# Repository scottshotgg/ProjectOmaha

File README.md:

# ProjectOmaha - Senior Design
## Software
### How to login
Authentication was recently added. Use username "admin" and password "password" to login.
### How to run the server
#### Windows
1. run `scripts/windows/run.bat`
2. If running for the first time, restart the command line and run again. (environment variables need to be refreshed)

#### Linux / OS X
Just execute `scripts/run`
### Debug Mode
Run the server in debug mode by executing `scripts/run -d 1`. If you're on windows, the command is `go run main.go -d 1`. Running in debug mode will cut out the microcontroller. All changes in state are just made in memory.

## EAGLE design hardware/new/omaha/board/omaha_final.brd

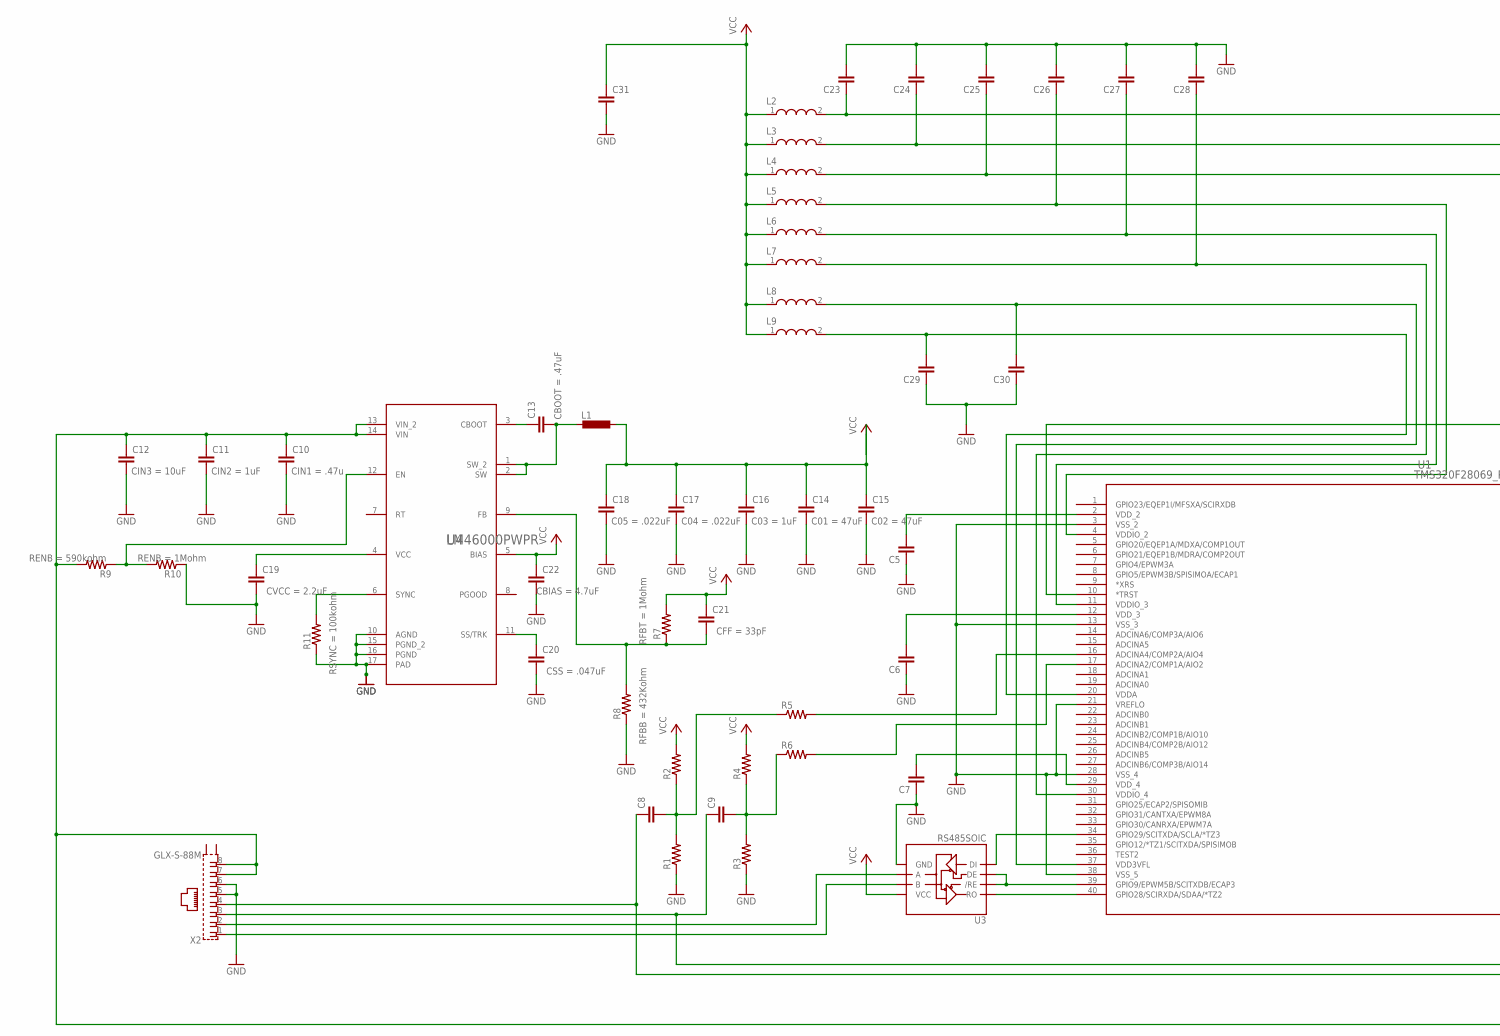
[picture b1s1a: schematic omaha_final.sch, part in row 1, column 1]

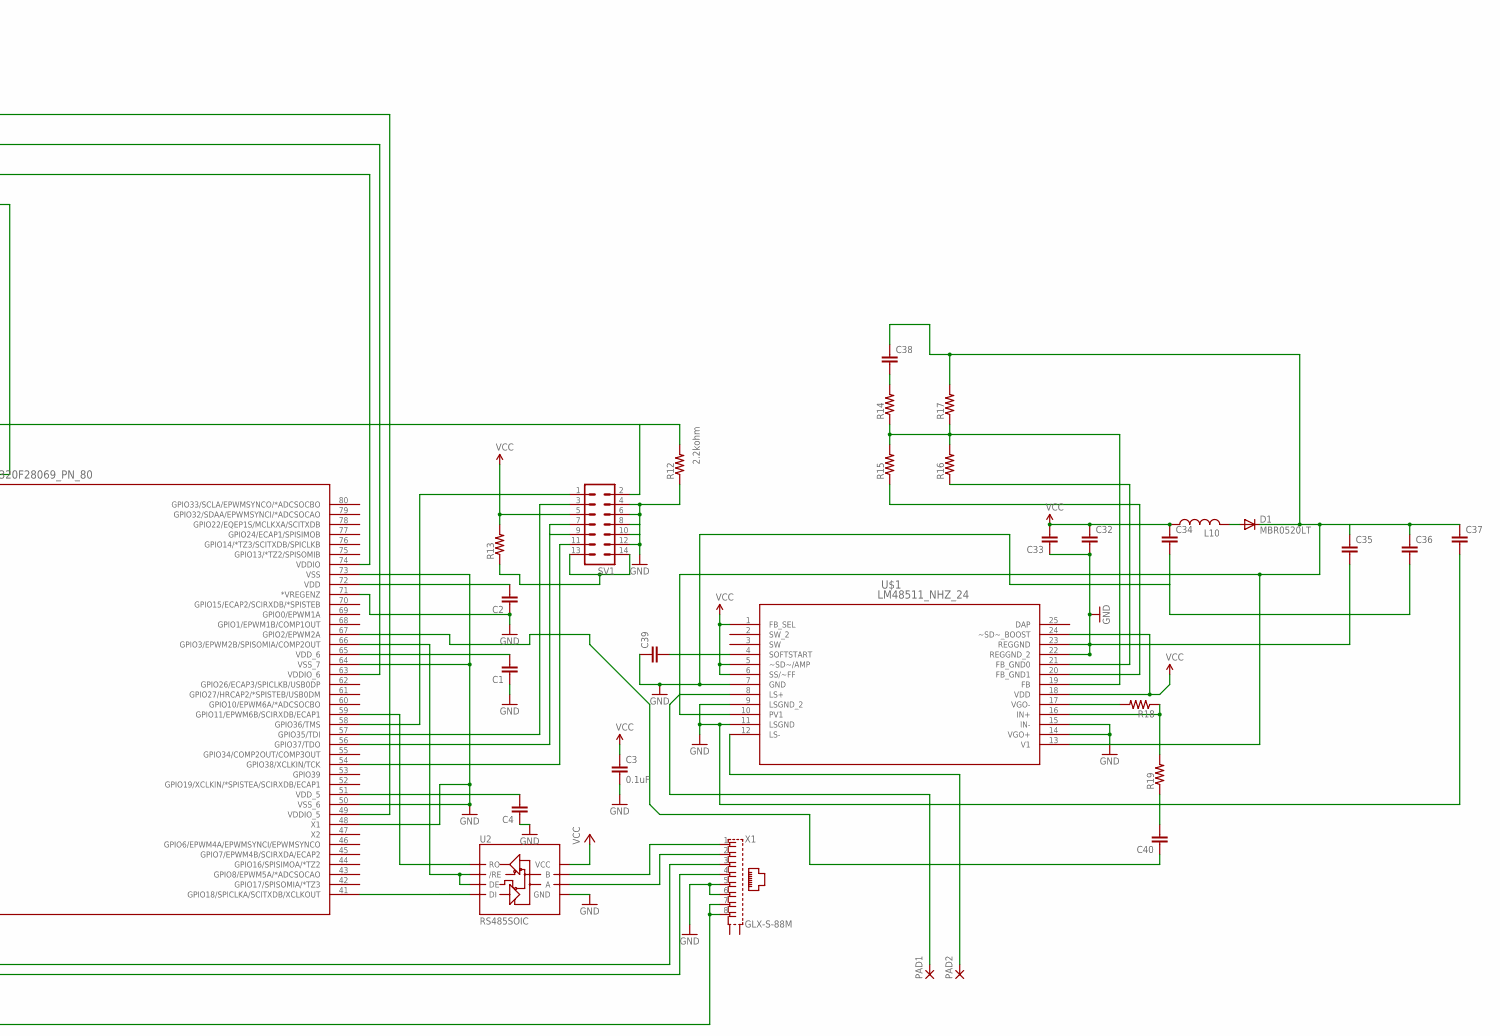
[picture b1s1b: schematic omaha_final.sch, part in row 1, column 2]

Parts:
C1, C2, C4, C5, C6, C7, C8, C9, C19, C20, C21, C23, C24, C25, C26, C27, C28, C29, C30, C31: C-EUC0603; C0603
C3: 0.1uF; 0603-CAP
C10, C13, C16, C17, C18, C22, C32, C33, C34, C35, C36, C37, C38, C39, C40: C-EUC0805; C0805
C11, C14, C15: C-EUC1210; C1210
C12: C-EUC2220K; C2220K
D1: MBR0520LT; SOD123
L1: DO3316P
L2, L3, L4, L5, L6, L7, L8, L9: WE-KI_0805A
L10: L-USL5650M; L5650M
PAD1, PAD2: 3,81/1,4
R1, R2, R3, R4, R5, R6, R7, R8, R9, R10, R11, R12, R13: R-US_R0603; R0603
R14, R15, R16, R17, R18, R19: R-US_R0805; R0805
SV1: MA07-2W
U1: TMS320F28069_PN_80; PN80
U2, U3: RS485SOIC; SO08
U4: LM46000PWPR; PWP0016F
U$1: LM48511_NHZ_24; SQA24B
X1, X2: GLX-S-88M

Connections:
DAP: U$1.25 (DAP)
GND: C1.1, C2.1, C3.2, C4.1, C5.1, C6.1, C7.1, C10.2, C11.2, C12.2, C14.2, C15.2, C16.2, C17.2, C18.2, C19.2, C20.2, C22.2, C23.2, C24.2, C25.2, C26.2, C27.2, C28.2, C29.1, C30.1, C31.2, C32.2, C33.1, C34.2, C35.2, C36.2, C37.2, C39.1, R1.1, R3.1, R8.1, R10.1, R11.1, R12.1, SV1.4, SV1.6, SV1.8, SV1.10, SV1.12, U1.3 (VSS_2), U1.13 (VSS_3), U1.21 (VREFLO), U1.28 (VSS_4), U1.38 (VSS_5), U1.48 (X1), U1.50 (VSS_6), U1.64 (VSS_7), U1.71 (*VREGENZ), U1.73 (VSS), U2.5 (GND), U3.5 (GND), U4.10 (AGND), U4.15 (PGND_2), U4.16 (PGND), U4.17 (PAD), U$1.7 (GND), U$1.9 (LSGND_2), U$1.11 (LSGND), U$1.14 (VGO+), U$1.15 (IN-), U$1.22 (REGGND_2), U$1.23 (REGGND), X1.5, X1.6, X2.5, X2.6
unnamed: U1.59 (GPIO11/EPWM6B/SCIRXDB/ECAP1), U2.1 (RO)
unnamed: U1.34 (GPIO29/SCITXDA/SCLA/*TZ3), U3.4 (DI)
unnamed: U1.41 (GPIO18/SPICLKA/SCITXDB/XCLKOUT), U2.4 (DI)
unnamed: U1.40 (GPIO28/SCIRXDA/SDAA/*TZ2), U3.1 (RO)
unnamed: C1.2, U1.65 (VDD_6)
unnamed: C2.2, U1.72 (VDD)
unnamed: C4.2, U1.51 (VDD_5)
unnamed: C5.2, U1.2 (VDD_2)
unnamed: C6.2, U1.12 (VDD_3)
unnamed: C7.2, U1.29 (VDD_4)
unnamed: U2.7 (B), X1.1
unnamed: U2.6 (A), X1.2
unnamed: U3.7 (B), X2.1
unnamed: U3.6 (A), X2.2
unnamed: C9.1, X1.3, X2.3
unnamed: C8.1, X1.4, X2.4
unnamed: C8.2, R1.2, R2.1, R5.1
unnamed: C9.2, R3.2, R4.1, R6.1
unnamed: R6.2, U1.17 (ADCINA2/COMP1A/AIO2)
unnamed: R5.2, U1.16 (ADCINA4/COMP2A/AIO4)
unnamed: C13.2, L1.1, U4.1 (SW_2), U4.2 (SW)
unnamed: C10.1, C11.1, C12.1, R9.2, U4.13 (VIN_2), U4.14 (VIN), X1.7, X1.8, X2.7, X2.8
unnamed: C13.1, U4.3 (CBOOT)
unnamed: C19.1, U4.4 (VCC)
unnamed: C20.1, U4.11 (SS/TRK)
unnamed: C21.2, R7.1, R8.2, U4.9 (FB)
unnamed: R9.1, R10.2, U4.12 (EN)
unnamed: R11.2, U4.6 (SYNC)
unnamed: SV1.3, U1.57 (GPIO35/TDI)
unnamed: C24.1, L3.2, U1.63 (VDDIO_6)
unnamed: C28.1, L7.2, U1.30 (VDDIO_4)
unnamed: C25.1, L4.2, U1.74 (VDDIO)
unnamed: SV1.7, SV1.9, U1.56 (GPIO37/TDO)
unnamed: SV1.11, U1.54 (GPIO38/XCLKIN/TCK)
unnamed: C30.2, L8.2, U1.37 (VDD3VFL)
unnamed: R13.1, SV1.13, SV1.14
unnamed: C27.1, L6.2, U1.11 (VDDIO_3)
unnamed: C26.1, L5.2, U1.4 (VDDIO_2)
unnamed: C29.2, L9.2, U1.20 (VDDA)
unnamed: C23.1, L2.2, U1.49 (VDDIO_5)
unnamed: R12.2, SV1.2, U1.10 (*TRST)
unnamed: SV1.1, U1.58 (GPIO36/TMS)
unnamed: U1.39 (GPIO9/EPWM5B/SCITXDB/ECAP3), U3.2 (/RE), U3.3 (DE)
unnamed: D1.A, L10.2
unnamed: C35.1, C36.1, C37.1, C38.1, D1.C, R17.2, U$1.10 (PV1), U$1.13 (V1)
unnamed: C40.2, R19.1
unnamed: C38.2, R14.2
unnamed: R14.1, R15.2, R16.2, R17.1, U$1.19 (FB)
unnamed: C40.1, U1.67 (GPIO2/EPWM2A)
unnamed: R16.1, U$1.21 (FB_GND0)
unnamed: R15.1, U$1.20 (FB_GND1)
unnamed: C39.2, U$1.4 (SOFTSTART)
unnamed: R18.2, U$1.17 (VGO-)
unnamed: R18.1, R19.2, U$1.16 (IN+)
unnamed: PAD1.1, U$1.8 (LS+)
unnamed: PAD2.1, U$1.12 (LS-)
RTS: U1.66 (GPIO3/EPWM2B/SPISOMIA/COMP2OUT), U2.2 (/RE), U2.3 (DE)
VCC: C3.1, C14.1, C15.1, C16.1, C17.1, C18.1, C21.1, C22.1, C31.1, C32.1, C33.2, C34.1, L1.2, L2.1, L3.1, L4.1, L5.1, L6.1, L7.1, L8.1, L9.1, L10.1, R2.2, R4.2, R7.2, R13.2, SV1.5, U2.8 (VCC), U3.8 (VCC), U4.5 (BIAS), U$1.1 (FB_SEL), U$1.5 (~SD~/AMP), U$1.6 (SS/~FF), U$1.18 (VDD), U$1.24 (~SD~_BOOST)

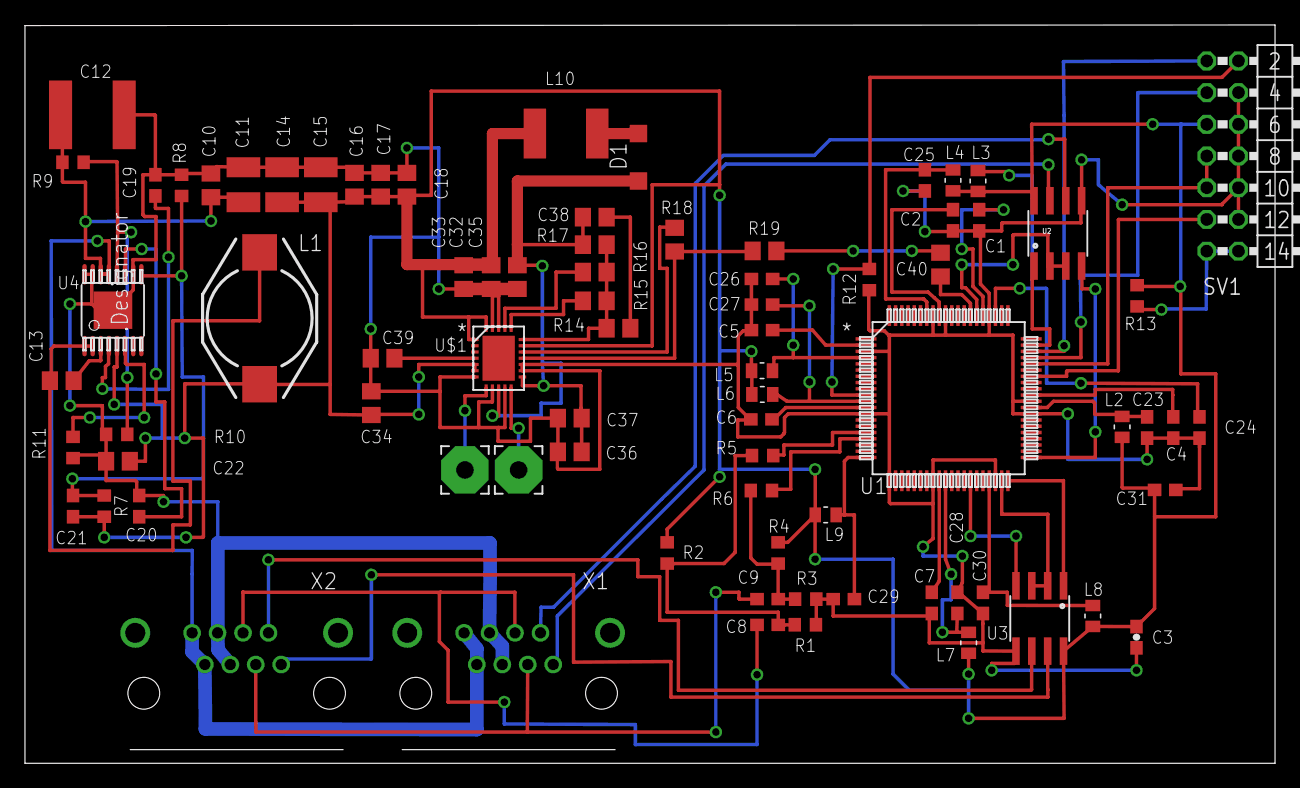
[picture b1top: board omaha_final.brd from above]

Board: 2 copper layers, 100.2 x 59.1 mm, 80 parts (0 on the bottom side), 59 nets.

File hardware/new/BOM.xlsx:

|  |  | Total Item Count: |  | 75
Omaha REV 0.1 BOM
 | Microcontroller System | Name | Size | Value | Notes |  |  | Power System | Name | Size | Value | Notes |  |  | Amplifier System | Name | Size | Value | Notes
 |  | C1 | SMD 0603 | 2.2uF |  |  |  |  | C10 | SMD 0805 | .47uF |  |  |  |  | C32 | SMD 0805 | 1uF
 |  | C2 | SMD 0603 | 2.2uF |  |  |  |  | C11 | SMD 1210 | 1uF |  |  |  |  | C33 | SMD 0805 | 10uF
 |  | C3 | SMD 0603 | 0.1uF |  |  |  |  | C12 | SMD 2220 | 10uF |  |  |  |  | C34 | SMD 0805 | 1uF
 |  | C4 | SMD 0603 | 2.2uF |  |  |  |  | C13 | SMD 0805 | .47uF |  |  |  |  | C35 | SMD 0805 | 100uF
 |  | C5 | SMD 0603 | 2.2uF |  |  |  |  | C14 | SMD 1210 | 47uF |  |  |  |  | C36 | SMD 0805 | 1uF
 |  | C6 | SMD 0603 | 2.2uF |  |  |  |  | C15 | SMD 1210 | 47uF |  |  |  |  | C37 | SMD 0805 | 1uF
 |  | C7 | SMD 0603 | 2.2uF |  |  |  |  | C16 | SMD 0805 | 1uF |  |  |  |  | C38 | SMD 0805 | 280pF
 |  | C8 | SMD 0603 | 2.2uF |  |  |  |  | C17 | SMD 0805 | .022uF |  |  |  |  | C39 | SMD 0805 | 100nF
 |  | C9 | SMD 0603 | 2.2uF |  |  |  |  | C18 | SMD 0805 | .022uF |  |  |  |  | C40 | SMD 0805 | 80nF
 |  | C23 | SMD 0603 | 2.2uF |  |  |  |  | C19 | SMD 0603 | 2.2uF |  |  |  |  | R14 | SMD 0805 | 2.5kohm
 |  | C24 | SMD 0603 | 2.2uF |  |  |  |  | C20 | SMD 0603 | .047uF |  |  |  |  | R15 | SMD 0805 | 4.87kohm
 |  | C25 | SMD 0603 | 2.2uF |  |  |  |  | C21 | SMD 0603 | 33pF |  |  |  |  | R16 | SMD 0805 | 9.31kohm
 |  | C26 | SMD 0603 | 2.2uF |  |  |  |  | C22 | SMD 0805 | 4.7uF |  |  |  |  | R17 | SMD 0805 | 25.5kohm
 |  | C27 | SMD 0603 | 2.2uF |  |  |  |  | R7 | SMD 0603 | 1Mohm |  |  |  |  | R18 | SMD 0805 | 20kohm
 |  | C28 | SMD 0603 | 2.2uF |  |  |  |  | R8 | SMD 0603 | 432kohm |  |  |  |  | R19 | SMD 0805 | 20kohm
 |  | C29 | SMD 0603 | 2.2uF |  |  |  |  | R9 | SMD 0603 | 590kohm |  |  |  |  | L10 | Not Listed | 6.8uH | IND_COILCRAFT-DO1813P
 |  | C30 | SMD 0603 | 2.2uF |  |  |  |  | R10 | SMD 0603 | 1Mohm |  |  |  |  | D1 | Not listed | MBR0520 IR | Eagle has library for device
 |  | C31 | SMD 0603 | 2.2uF |  |  |  |  | R11 | SMD 0603 | 100kohm
 |  | R1 | SMD 0603 | 1kohm |  |  |  |  | L1 | SMD
 |  | R2 | SMD 0603 | 1kohm
 |  | R3 | SMD 0603 | 1kohm
 |  | R4 | SMD 0603 | 1kohm
 |  | R5 | SMD 0603 | 56kohm
 |  | R6 | SMD 0603 | 56kohm
 |  | R12 | SMD 0603 | 2.2kohm
 |  | R13 | SMD 0603 | 2.2kohm
 |  | L2 | SMD 0805 | Not Listed | BPB2125HS600-T
 |  | L3 | SMD 0805 | Not Listed | BPB2125HS600-T
 |  | L4 | SMD 0805 | Not Listed | BPB2125HS600-T
 |  | L5 | SMD 0805 | Not Listed | BPB2125HS600-T
 |  | L6 | SMD 0805 | Not Listed | BPB2125HS600-T
 |  | L7 | SMD 0805 | Not Listed | BKB2125HS600-T
 |  | L8 | SMD 0805 | Not Listed | BLM21PG221SN1D
 |  | Quanity | Link |  |  |  |  |  | Size | Value | Count | Link
Microcontroller | TMS320f28069 | 1 | http://www.mouser.com/ProductDetail/Texas-Instruments/TMS320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 |  |  |  |  | Capacitor type 1 | SMD 0603 | 2.2uF | 18 | http://www.mouser.com/ProductDetail/Murata-Electronics/GRJ18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
DC/DC Buck Converter | LM46000 | 1 | http://www.mouser.com/ProductDetail/Texas-Instruments/LM4600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 |  |  |  |  | Capacitor type 2 | SMD 0603 | 0.1uF | 1 | http://www.mouser.com/ProductDetail/Murata-Electronics/GRJ18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
Class D amplifier | LM48511 | 1 | http://www.mouser.com/ProductDetail/Texas-Instruments/LM4851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 |  |  |  |  | Capacitor type 3 | SMD 0603 | .047uF | 1 | http://www.mouser.com/ProductDetail/Murata-Electronics/GRJ18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
Interface | RJ45 Jack | 2 | http://www.mouser.com/ProductDetail/TE-Connectivity-Corcom/R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 |  |  |  |  | Capacitor type 4 | SMD 0603 | 33pF | 1 | http://www.mouser.com/ProductDetail/AVX/06031A330FAT2A/?qs=s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
SP3485 | RS485 Transciever | 2 | http://www.mouser.com/ProductDetail/Exar/SP3485EN-L-TR/?qs=s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 |  |  |  |  | Capacitor type 5 | SMD 0805 | .47uF | 2 | http://www.mouser.com/ProductDetail/Murata-Electronics/GRJ21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
 | JTAG Programmer link | 1 | http://www.amazon.com/2-54mm-Download-Header-Socket-DC3-16P/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 |  |  |  |  | Capacitor type 6 | SMD 0805 | 1uF | 5 | http://www.mouser.com/ProductDetail/Murata-Electronics/GRJ21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
 |  |  |  |  |  |  |  | Capacitor type 7 | SMD 0805 | .022uF | 2 | http://www.mouser.com/ProductDetail/TDK/C2012X7R2E223K125AA/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
 |  |  |  |  |  |  |  | Capacitor type 8 | SMD 0805 | 4.7uF | 1 | http://www.mouser.com/ProductDetail/Murata-Electronics/GRJ21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
 |  |  |  |  |  |  |  | Capacitor type 9 | SMD 0805 | 10uF | 1 | http://www.mouser.com/ProductDetail/Murata-Electronics/GRJ21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
 |  |  |  |  |  |  |  | Capacitor type 10 | SMD 0805 | 100uF | 1 | http://www.mouser.com/ProductDetail/Murata-Electronics/GRM21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
 |  |  |  |  |  |  |  | Capacitor type 11 | SMD 0805 | 100nF | 1 | http://www.mouser.com/ProductDetail/Murata-Electronics/GRJ21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
 |  |  |  |  |  |  |  | Capacitor type 12 | SMD 0805 | 280pF | 1 | http://www.mouser.com/ProductDetail/Murata-Electronics/GRM21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
 |  |  |  |  |  |  |  | Capacitor type 13 | SMD 0805 | 80nF | 1 | http://www.mouser.com/ProductDetail/AVX/08055C823KAT2A/?qs=s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
 |  |  |  |  |  |  |  | Capacitor type 14 | SMD 1210 | 1uF | 1 | http://www.mouser.com/ProductDetail/AVX/SQCB7M0R1BATME/?qs=s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
 |  |  |  |  |  |  |  | Capacitor type 15 | SMD 1210 | 47uF | 2 | http://www.mouser.com/ProductDetail/Murata-Electronics/GRJ32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
 |  |  |  |  |  |  |  | Capacitor type 16 | SMD 2220 | 10uF | 1 | http://www.mouser.com/ProductDetail/AVX/22205C106MAT2A/?qs=s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
 |  |  |  |  |  |  |  | Resistor type one | SMD 0603 | 1kohm | 4 | http://www.mouser.com/ProductDetail/Vishay-Dale/CRCW06031K00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
 |  |  |  |  |  |  |  | Resistor type two | SMD 0603 | 56kohm | 2 | http://www.mouser.com/ProductDetail/Panasonic/ERA-3AED560V/?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
 |  |  |  |  |  |  |  | Resistor type three | SMD 0603 | 2.2kohm | 2 | http://www.mouser.com/ProductDetail/KOA-Speer/RK73H1JTTD2201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
 |  |  |  |  |  |  |  | Resistor Type Four | SMD 0603 | 1Mohm | 2 | http://www.mouser.com/ProductDetail/TE-Connectivity-Neohm/CP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
 |  |  |  |  |  |  |  | Resistor type five | SMD 0603 | 590kohm | 1 | http://www.mouser.com/ProductDetail/Vishay-Dale/CRCW0603590K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
 |  |  |  |  |  |  |  | Resistor type six | SMD 0603 | 432kohm | 1 | http://www.mouser.com/ProductDetail/Vishay-Dale/CRCW0603432K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
 |  |  |  |  |  |  |  | Resistor type seven | SMD 0603 | 100kohm | 1 | http://www.mouser.com/ProductDetail/Vishay-Dale/CRCW0603100R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
 |  |  |  |  |  |  |  | Resistor type eight | SMD 0805 | 2.5kohm | 1 | http://www.mouser.com/ProductDetail/Panasonic/ERA-3ARB2491V/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
 |  |  |  |  |  |  |  | Resistor type nine | SMD 0805 | 4.87kohm | 1 | http://www.mouser.com/ProductDetail/Panasonic/ERA-3AEB4871V/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
 |  |  |  |  |  |  |  | Resistor type ten | SMD 0805 | 9.31kohm | 1 | http://www.mouser.com/ProductDetail/Bourns/CR0603-FX-9311ELF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
 |  |  |  |  |  |  |  | Resistor type 11 | SMD 0805 | 25.5kohm | 1 | http://www.mouser.com/ProductDetail/Vishay-Dale/CRCW060325R5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
 |  |  |  |  |  |  |  | Resistor type 12 | SMD 0805 | 20kohm | 2 | http://www.mouser.com/ProductDetail/KOA-Speer/RK73H1JTTD2002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
 |  |  |  |  |  |  |  | Inductor type 1 | NA | NA | 1 | http://www.mouser.in/ProductDetail/Coiltronics-Eaton/MPIA404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
 |  |  |  |  |  |  |  | Inductor type 2 | SMD 0805 | NA | 7 | http://www.mouser.com/ProductDetail/Taiyo-Yuden/BKP2125HS600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
 |  |  |  |  |  |  |  | Inductor type 3 | NA | 6.8uH | 1 | http://www.mouser.com/ProductDetail/Murata-Electronics/BLM21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
 |  |  |  |  |  |  |  | Inductor type 4 |  |  |  | http://www.mouser.com/Search/ProductDetail.aspx?R=IHLP2525CZ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
 |  |  |  |  |  |  |  | Diode | NA | NA | 1 | http://www.mouser.com/ProductDetail/ON-Semiconductor/MBR0520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
 |  |  |  |  |  |  |  |  |  |  | 69

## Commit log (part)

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2015-09-10 repo init
2015-09-23 restructured the repo
2015-09-23 created a simple web server that serves an index template file and added some startup scripts.
2015-09-23 removed another README
2015-09-25 added demo handlers
2015-09-25 changed to start/stop demo
2015-10-08 Does this message work?
2015-10-08 Added DemoLEDHandler
2015-10-09 small syntax error fix
2015-10-09 added a LED demo
2015-10-09 Refactored code, added debug mode, and removed dependency on jquery
2015-10-10 Added a map controller and updated the UI to serve multiple pages
2015-10-12 refactored the code a bit more
2015-10-12 improved animations
2015-10-12 updated hard coded ID
2015-10-13 fixing light controller ajax
2015-10-13 added some debugging prints
2015-10-13 fixed data comparison bug
2015-10-15 Added a handler
2015-10-15 I messed up some stuff on the handlers
2015-10-15 auto thing
2015-10-15 changed the code to show scott how to handle javascript input
2015-10-15 revert changes made to show scott some stuff
2015-10-15 removed unused files
2015-10-15 fixed gitignore conflicts
2015-10-15 put back another change
2015-10-15 updated gitignore to ignore go dirs
2015-10-15 removed unnecessary dirs
2015-10-17 Fixed some stuff and made some changhed and improvments to the protocol
2015-10-17 MAX HELP ME; light-controller.html line 43, wtf is id
2015-10-17 Updated volume selector handling
2015-10-18 Made some handlers for other commands
2015-10-18 worked on some more stuff
2015-10-18 MAXXXX: I worked on a map for the AreYouALive function, how does this go back to the frontend? Look in controller.go and demoHandlers.go all the way at the bottom on both. Also I think we have a prob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
2015-10-18 checking in my changes
2015-10-18 added size parameter to header function
2015-10-19 fixed initialization bug
2015-10-19 added ControllerStatus. Some stuff is hard coded to work in the UI. Need to fix that.
2015-10-19 added GenericHandlers
2015-10-19 added generic responses
2015-10-20 added port initialization
2015-10-20 added an averaging filter handler
2015-10-20 added paper-dropdown-menu
2015-10-20 add averaging controller
2015-10-20 updated the averaging controller to make it look better
2015-10-20 prep for the demo
2015-10-22 Trying to understand and implement the new way of sending data. I also set up the new serial package that we are using. We may need a try-catch or something for the EOF error that you will get when t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
2015-10-26 updated the UI
2015-10-26 added db init code
2015-10-26 updated omaha-app properties
2015-10-26 Nevermind the last commit message, I figured a lot of that stuff out. What I am stuck on now is that the speakerId in averaging-controller.html is undefined for some reason and thus the handler in sp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
2015-10-26 OMG OMG OMG OMG I did it. I got it. LIKE A BOSS. I did the volume thing. It was literally one line that I was forgetting about in audio-controller.html. <averaging-controller id=averaging speaker-id=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
2015-10-26 just checking in nonsense
2015-10-26 uncommented port write
2015-10-28 created a volume touch UI
2015-10-28 refactored audio-controller and light-controller
2015-10-28 refactored the volume-selector
2015-10-28 updated the UI to select speakers by clicking on the map
2015-10-30 changed the speaker icon, removed the menu button, and added a back button to the speaker page
2015-10-30 added some animations to the map/audio controller
2015-10-30 Updated PUTTY variable for debug and added a gew more commands.
2015-10-30 HARDWARE: Added new commands, changed soem other commands, (just the letter), and added in PuTTY #define for debugging in PuTTY. SOFTWARE: Testing minor changes to constants.go to reflect hwardware c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
2015-10-30 fixed the map on click
2015-10-31 updated map and audio controller
2015-10-31 updated the map to scale well
2015-10-31 Updated main to with some comments.
2015-11-01 added my code back in to fix the scaling issues
2015-11-02 fixed a bug in main.go
2015-11-02 White listed the machine the server is running on
2015-11-02 Updated the appearance of the speaker icons. The icons are now white with a colored circular background
2015-11-02 fixed undefined error in volume-selector
2015-11-02 Cleaned up the system init code
2015-11-04 added image processing script
2015-11-06 Added speakers to the database, colored the available speakers green in the UI, added image processing to the run script, and updated the backend to get speakers from the DB
2015-11-07 Updated some hardware stuff
2015-11-07 updated SCI communications
2015-11-08 Trying to fix port read error
2015-11-08 Update to hardware
2015-11-08 added account creation and removed the hard coded coordinates from the UI
2015-11-10 Added some commands, looked at writing to flash (read comments by case 'W') and also thought about usign an ID-less system
2015-11-10 I am rethinking the reset commands, we may not even want to use them. Read the last commit message.
2015-11-14 moved the menu icon
2015-11-16 Added an omaha drawer
2015-11-17 Added the realtive addressing into the protocol and reworked it to look a bit nicer
2015-11-19 For some reason it still isn't working. The speakerLocations.txt file has nothing in it, but as far as I can see the program should be working. I am not sure why it isn't. We should try to fix this b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
2015-11-21 Uploading a speakerLocations file to the repo
2015-11-21 added some comments to the code
2015-11-21 updated the speaker handling
2015-11-21 Added bulk zone fetching functions
2015-11-21 removed the in memory controller map
2015-11-21 Added zone creation to the UI
2015-11-29 updated the zone functions to get the zone name
2015-12-01 Test comment
    Testing push stuff.
2015-12-01 updated git ignore
2015-12-01 updated gitignore
2015-12-05 updated database code to use transactions on init
2015-12-06 The map now color codes speakers by zone
2015-12-07 removed unused element
2015-12-07 Added a help panel
2015-12-07 Made speaker-controller mode changes more elegant
2015-12-08 fixed tooltip styling
2015-12-08 fixed the styling of the drawer
2016-01-22 updating the equalizer backend
2016-01-22 last fucking time i fix this fucking file
2016-01-22 added some comments about changing the css
2016-01-22 changing the placement of the todo.readme
2016-01-22 removed zone byte; changed to 3 bytes instead of 4
2016-01-23 updated todo.readme
2016-01-27 1/26: finished multiple volume sliders, started fixing paging sliders, did some ui work
2016-01-28 added in a serial port flag
2016-01-29 added sound masking volume
2016-01-29 all this shit is working now. Adding the handler to retrieve information from the backend for the frontend
2016-01-31 fixed the click event for the get handler
2016-02-02 fix the clicks, shit
2016-02-06 MILESTONE 1: Individual UI loads on first view from the database, everything working
2016-02-12 HARDWARE: Uploading new code base into the new folder, stashing old code in the old folder. BOM and board files are also included. SOFTWARE: Modified database schema, fixed animations, figured out da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
2016-02-16 updated the sliders for the current values and stuff, small improvements
2016-02-17 randomly thought about the paper-item deletion code and thought that the check really doesnt need to be there; realistically, if you just analyze the statistical probability that the check is getting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
2016-02-19 preset shit is done, works but not rigorously tested
2016-02-19 did something cool, cant even remember anymore, fix the setting currentyl applied and dont allow them to actually select to add a new preset without actually selecting one
2016-02-19 fixed the equalizer styling mostly
2016-02-22 made equalizer larger and it still scaled well, quick-fixed the SendPagingRequest function, tryign to get FF to work
2016-02-22 changed all the blue color codes to #3f51b5, still need to fix the increment/decrement stuff for the pages with multiple sliders, and need to fix the tooltip not showing stuff, make the sliders alway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
2016-02-24 target page made, adding presets fixed, added a select interaction in the zone controller, fixed the tooltip to display everything; still need to add zone names, changed the database to pull the name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
2016-02-25 target_selector.html has been fixed up to look better and the remenants of voluem_selector has been scrubbed. Changed some stuff in speakerHandlers, small comment change in equalizer_controller
2016-02-26 made the database accept the additions, modified the handler for it a bit, modified the getInsertSpeakerStatement function
2016-02-27 fixed the mpa controller selecting double the speakers, we need to add only mutually exclusive speakers to the map
2016-03-01 fixed something very minor that was messing with the delete ability where it was not deleting the correct speaker
2016-03-01 Changed the sort routine to merge sort, made the injection faster, no longer looking up stuff everytime we inject
2016-03-05 lots of stuff today, added entire Target adding handlers, added function call to create the table for targets in init.go, added SaveTarget into speakers.go, changed stuff in averaging-controller, cha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
2016-03-12 added favicon.ico, added colors to the equalizer when invalid, added inputs to the equalizer and changed the tab sequence so that you can tab through them, updateSpeakerTarget now works, changed the 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
2016-03-16 made the frontend of the keep alive - this is controlled by the system status struct in the backend backend, added a handler to do this and a few functions
2016-03-17 updated the database to reflect the paging zone changes - added new functions in zones, init, and other pages, paging controller and information-viewer are now rendering and nothing is messed up, the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
2016-03-19 changed the comparison
2016-03-19 added a few printouts and changed what it detects
2016-03-19 added better printouts and changed the decimal band to 21 always to signify a decimal
2016-03-19 still working on the keepAlive stuff, got it to load the dead ones on startup, refreshing is a bitch though, still handling that, somthing is off by 1 into an array or something, idk, also look into 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
2016-03-25 cascading equalizer code for music, changes in the paging dialer and zone controller
2016-03-25 added a new flag, -c=x where x can equal any integer value and specifies the number of controllers in the line
2016-03-31 added cascading until the DB for equalizerMode, UI improvments when moving between modes, equalizerSwitch dialog is now dynamic, new handler - changeEQModeAjax, it not "remembers" what state the spea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
2016-04-02 reverted some of the equalizer changed in how the data is passed to the backend - still abstracted in the frontend the same way, added pagingZones being sent at initialization, made zones load into t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
2016-04-07 made some changes to the init to make it actually work, added zone to map gps animations - trying to get the remove to work
2016-04-16 added a scheduling controller into speaker controller, changed the paging controller and added some other things
2016-04-23 I cant even remember all of what I did. Fixed a few things and added the paging equalizer, added a hander or a few, added a scheduler to the frontend, fixed up the account creation form and made it l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
2016-05-03 Added scheduling panes, added the scheduling mode in the handlers, adde scheduling mode into the database but I'm not sure why, fixed permissions, bolded the sides, added the min and max for the volu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
2016-06-09 revision that will most likely go out to SPS
2016-06-10 GoLang code has been fully un-commented and "sanitized"
2016-06-17 Added documentation script and files that it creates.
2016-06-21 added more comments,cleaned some of the code, finished frontend generated documentation, added some backend generated documentation, need to add some features, take out zones, fix some styling, work 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
2016-06-22 added some UDP sending and recieving, uploading to go the rpi, also, remove the thing
2016-06-22 added backend support for the selector that is now manual addition instead of the automatic finder like before
2016-06-23 changes for rpi
2016-06-27 fixed some stuff, made the logout thing work, thresholds fixed - database problem, styling fixed
2016-07-11 login fix
2017-01-06 fixed some aniimation update stuff and some resources
2017-01-10 tested and working on the RPI, added a script on the Desktop called 'Start_Server_compiled' to use a compiled executable version of the server that is much faster and has a more consistent performanc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

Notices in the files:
parts and their libraries:
SparkFun-Capacitors: Licensing: Creative Commons ShareAlike 4.0 International - https://creativecommons.org/licenses/by-sa/4.0
EagleLibrary_Wuerth_Elektronik_eiSos_rev: Copyright: Würth Elektronik
